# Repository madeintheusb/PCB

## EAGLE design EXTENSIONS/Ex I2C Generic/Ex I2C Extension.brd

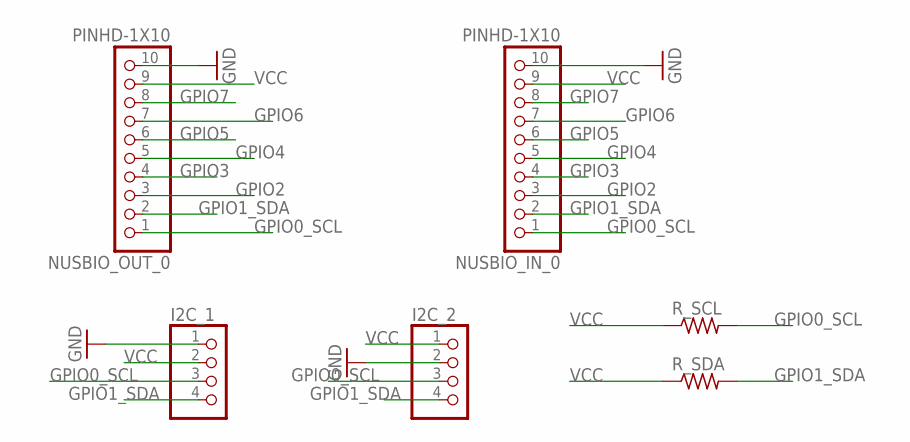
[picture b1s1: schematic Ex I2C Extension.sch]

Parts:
I2C_1, I2C_2: PINHD-1X4; 1X04
NUSBIO_IN_0: PINHD-1X10; 1X10-BIG
NUSBIO_OUT_0: PINHD-1X10; 1X10-BIG
R_SCL: R-US_R0805; R0805
R_SDA: R-US_R0805; R0805

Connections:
GND: I2C_1.1, I2C_2.2, NUSBIO_IN_0.10, NUSBIO_OUT_0.10
GPIO0_SCL: I2C_1.3, I2C_2.3, NUSBIO_IN_0.1, NUSBIO_OUT_0.1, R_SCL.2
GPIO1_SDA: I2C_1.4, I2C_2.4, NUSBIO_IN_0.2, NUSBIO_OUT_0.2, R_SDA.2
GPIO2: NUSBIO_IN_0.3, NUSBIO_OUT_0.3
GPIO3: NUSBIO_IN_0.4, NUSBIO_OUT_0.4
GPIO4: NUSBIO_IN_0.5, NUSBIO_OUT_0.5
GPIO5: NUSBIO_IN_0.6, NUSBIO_OUT_0.6
GPIO6: NUSBIO_IN_0.7, NUSBIO_OUT_0.7
GPIO7: NUSBIO_IN_0.8, NUSBIO_OUT_0.8
VCC: I2C_1.2, I2C_2.1, NUSBIO_IN_0.9, NUSBIO_OUT_0.9, R_SCL.1, R_SDA.1

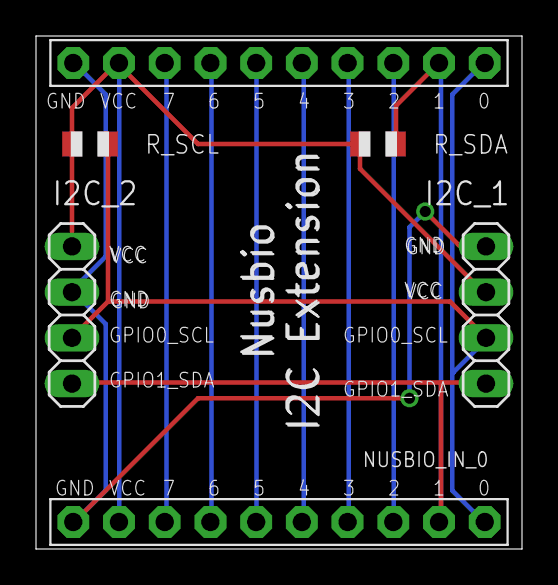
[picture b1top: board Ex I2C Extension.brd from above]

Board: 2 copper layers, 27.0 x 28.5 mm, 6 parts (0 on the bottom side), 10 nets.

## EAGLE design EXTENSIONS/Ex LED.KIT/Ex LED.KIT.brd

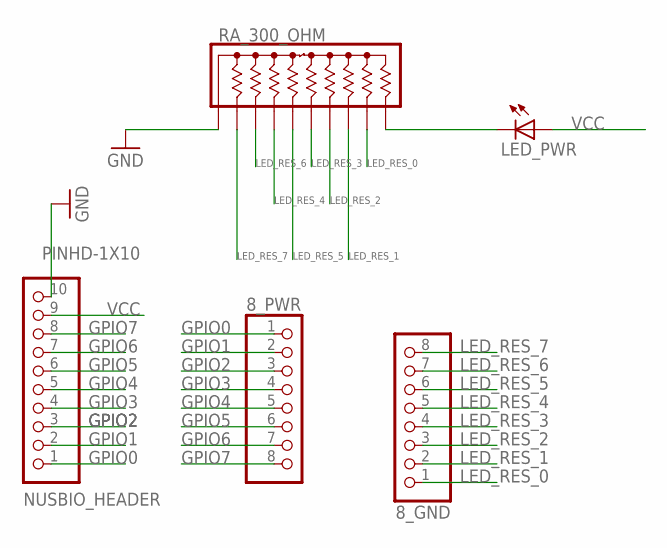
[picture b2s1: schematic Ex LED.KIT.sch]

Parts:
8_GND, 8_PWR: PINHD-1X8; 1X08
LED_PWR: LEDCHIPLED_0805; CHIPLED_0805
NUSBIO_HEADER: PINHD-1X10; 1X10-BIG
RA_300_OHM: 4610X; SIP10

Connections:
GND: NUSBIO_HEADER.10, RA_300_OHM.1
GPIO0: 8_PWR.1, NUSBIO_HEADER.1
GPIO1: 8_PWR.2, NUSBIO_HEADER.2
GPIO2: 8_PWR.3, NUSBIO_HEADER.3
GPIO3: 8_PWR.4, NUSBIO_HEADER.4
GPIO4: 8_PWR.5, NUSBIO_HEADER.5
GPIO5: 8_PWR.6, NUSBIO_HEADER.6
GPIO6: 8_PWR.7, NUSBIO_HEADER.7
GPIO7: 8_PWR.8, NUSBIO_HEADER.8
LED_RES_0: 8_GND.1, RA_300_OHM.9
LED_RES_1: 8_GND.2, RA_300_OHM.8
LED_RES_2: 8_GND.3, RA_300_OHM.7
LED_RES_3: 8_GND.4, RA_300_OHM.6
LED_RES_4: 8_GND.5, RA_300_OHM.4
LED_RES_5: 8_GND.6, RA_300_OHM.5
LED_RES_6: 8_GND.7, RA_300_OHM.3
LED_RES_7: 8_GND.8, RA_300_OHM.2
unnamed: LED_PWR.C, RA_300_OHM.10
VCC: LED_PWR.A, NUSBIO_HEADER.9

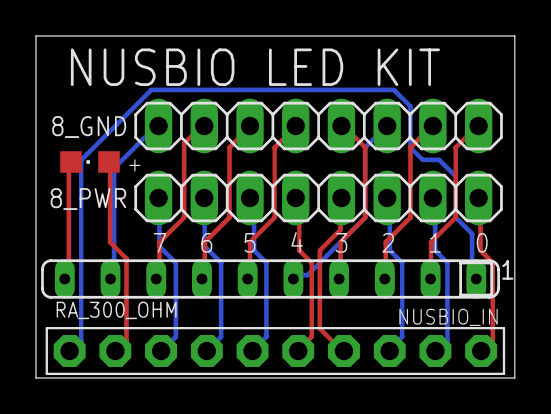
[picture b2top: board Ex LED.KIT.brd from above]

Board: 2 copper layers, 26.6 x 19.0 mm, 5 parts (0 on the bottom side), 19 nets.

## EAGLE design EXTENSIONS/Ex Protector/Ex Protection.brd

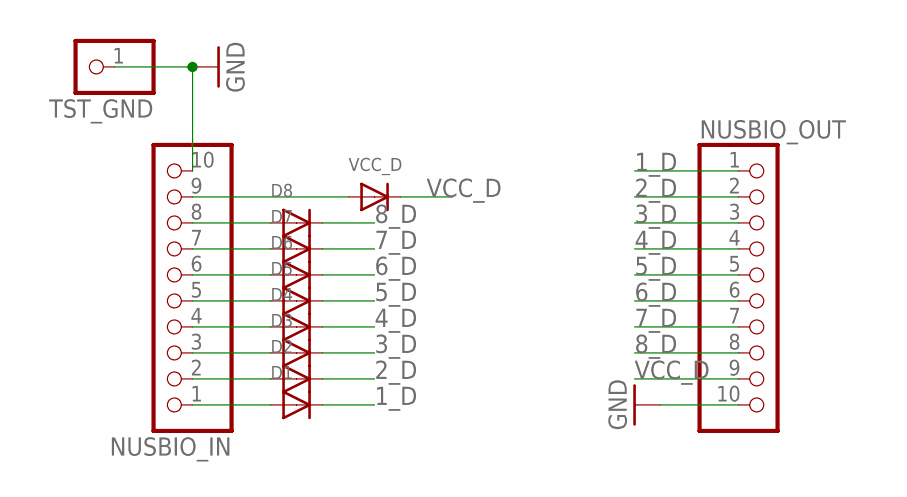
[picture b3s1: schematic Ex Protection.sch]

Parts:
D1, D2, D3, D4, D5, D6, D7, D8: DIODESOD-123; SOD-123
NUSBIO_IN: PINHD-1X10; 1X10-BIG
NUSBIO_OUT: PINHD-1X10; 1X10-BIG
TST_GND: PINHD-1X1; 1X01
VCC_D: DIODESOD-123; SOD-123

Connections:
1_D: D1.C, NUSBIO_OUT.1
2_D: D2.C, NUSBIO_OUT.2
3_D: D3.C, NUSBIO_OUT.3
4_D: D4.C, NUSBIO_OUT.4
5_D: D5.C, NUSBIO_OUT.5
6_D: D6.C, NUSBIO_OUT.6
7_D: D7.C, NUSBIO_OUT.7
8_D: D8.C, NUSBIO_OUT.8
GND: NUSBIO_IN.10, NUSBIO_OUT.10, TST_GND.1
unnamed: D1.A, NUSBIO_IN.1
unnamed: D2.A, NUSBIO_IN.2
unnamed: D3.A, NUSBIO_IN.3
unnamed: D4.A, NUSBIO_IN.4
unnamed: D5.A, NUSBIO_IN.5
unnamed: D6.A, NUSBIO_IN.6
unnamed: D7.A, NUSBIO_IN.7
unnamed: D8.A, NUSBIO_IN.8
unnamed: NUSBIO_IN.9, VCC_D.A
VCC_D: NUSBIO_OUT.9, VCC_D.C

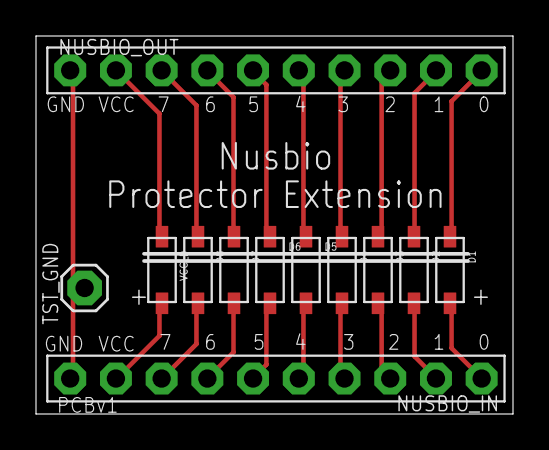
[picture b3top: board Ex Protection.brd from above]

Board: 2 copper layers, 26.5 x 21.0 mm, 12 parts (0 on the bottom side), 19 nets.

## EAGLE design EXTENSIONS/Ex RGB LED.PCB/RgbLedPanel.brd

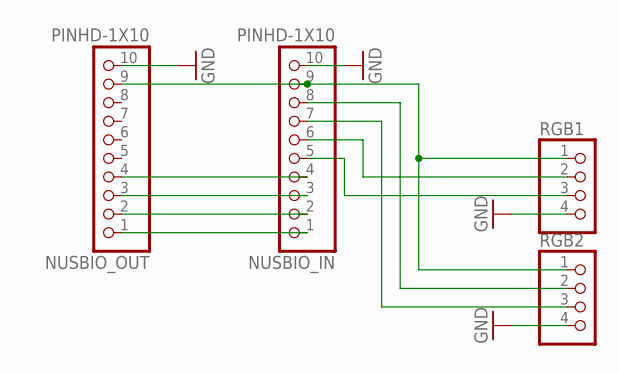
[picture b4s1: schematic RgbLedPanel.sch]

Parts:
NUSBIO_IN: PINHD-1X10; 1X10-BIG
NUSBIO_OUT: PINHD-1X10; 1X10-BIG
RGB1, RGB2: PINHD-1X4; 1X04

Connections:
GND: NUSBIO_IN.10, NUSBIO_OUT.10, RGB1.4, RGB2.4
unnamed: NUSBIO_IN.9, NUSBIO_OUT.9, RGB1.1, RGB2.1
unnamed: NUSBIO_IN.5, RGB1.3
unnamed: NUSBIO_IN.1, NUSBIO_OUT.1
unnamed: NUSBIO_IN.8, RGB2.2
unnamed: NUSBIO_IN.7, RGB2.3
unnamed: NUSBIO_IN.6, RGB1.2
unnamed: NUSBIO_IN.2, NUSBIO_OUT.2
unnamed: NUSBIO_IN.3, NUSBIO_OUT.3
unnamed: NUSBIO_IN.4, NUSBIO_OUT.4

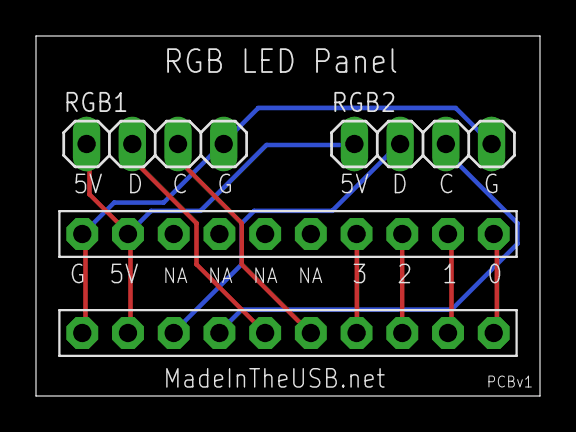
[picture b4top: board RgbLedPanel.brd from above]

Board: 2 copper layers, 28.0 x 20.0 mm, 4 parts (0 on the bottom side), 10 nets.
